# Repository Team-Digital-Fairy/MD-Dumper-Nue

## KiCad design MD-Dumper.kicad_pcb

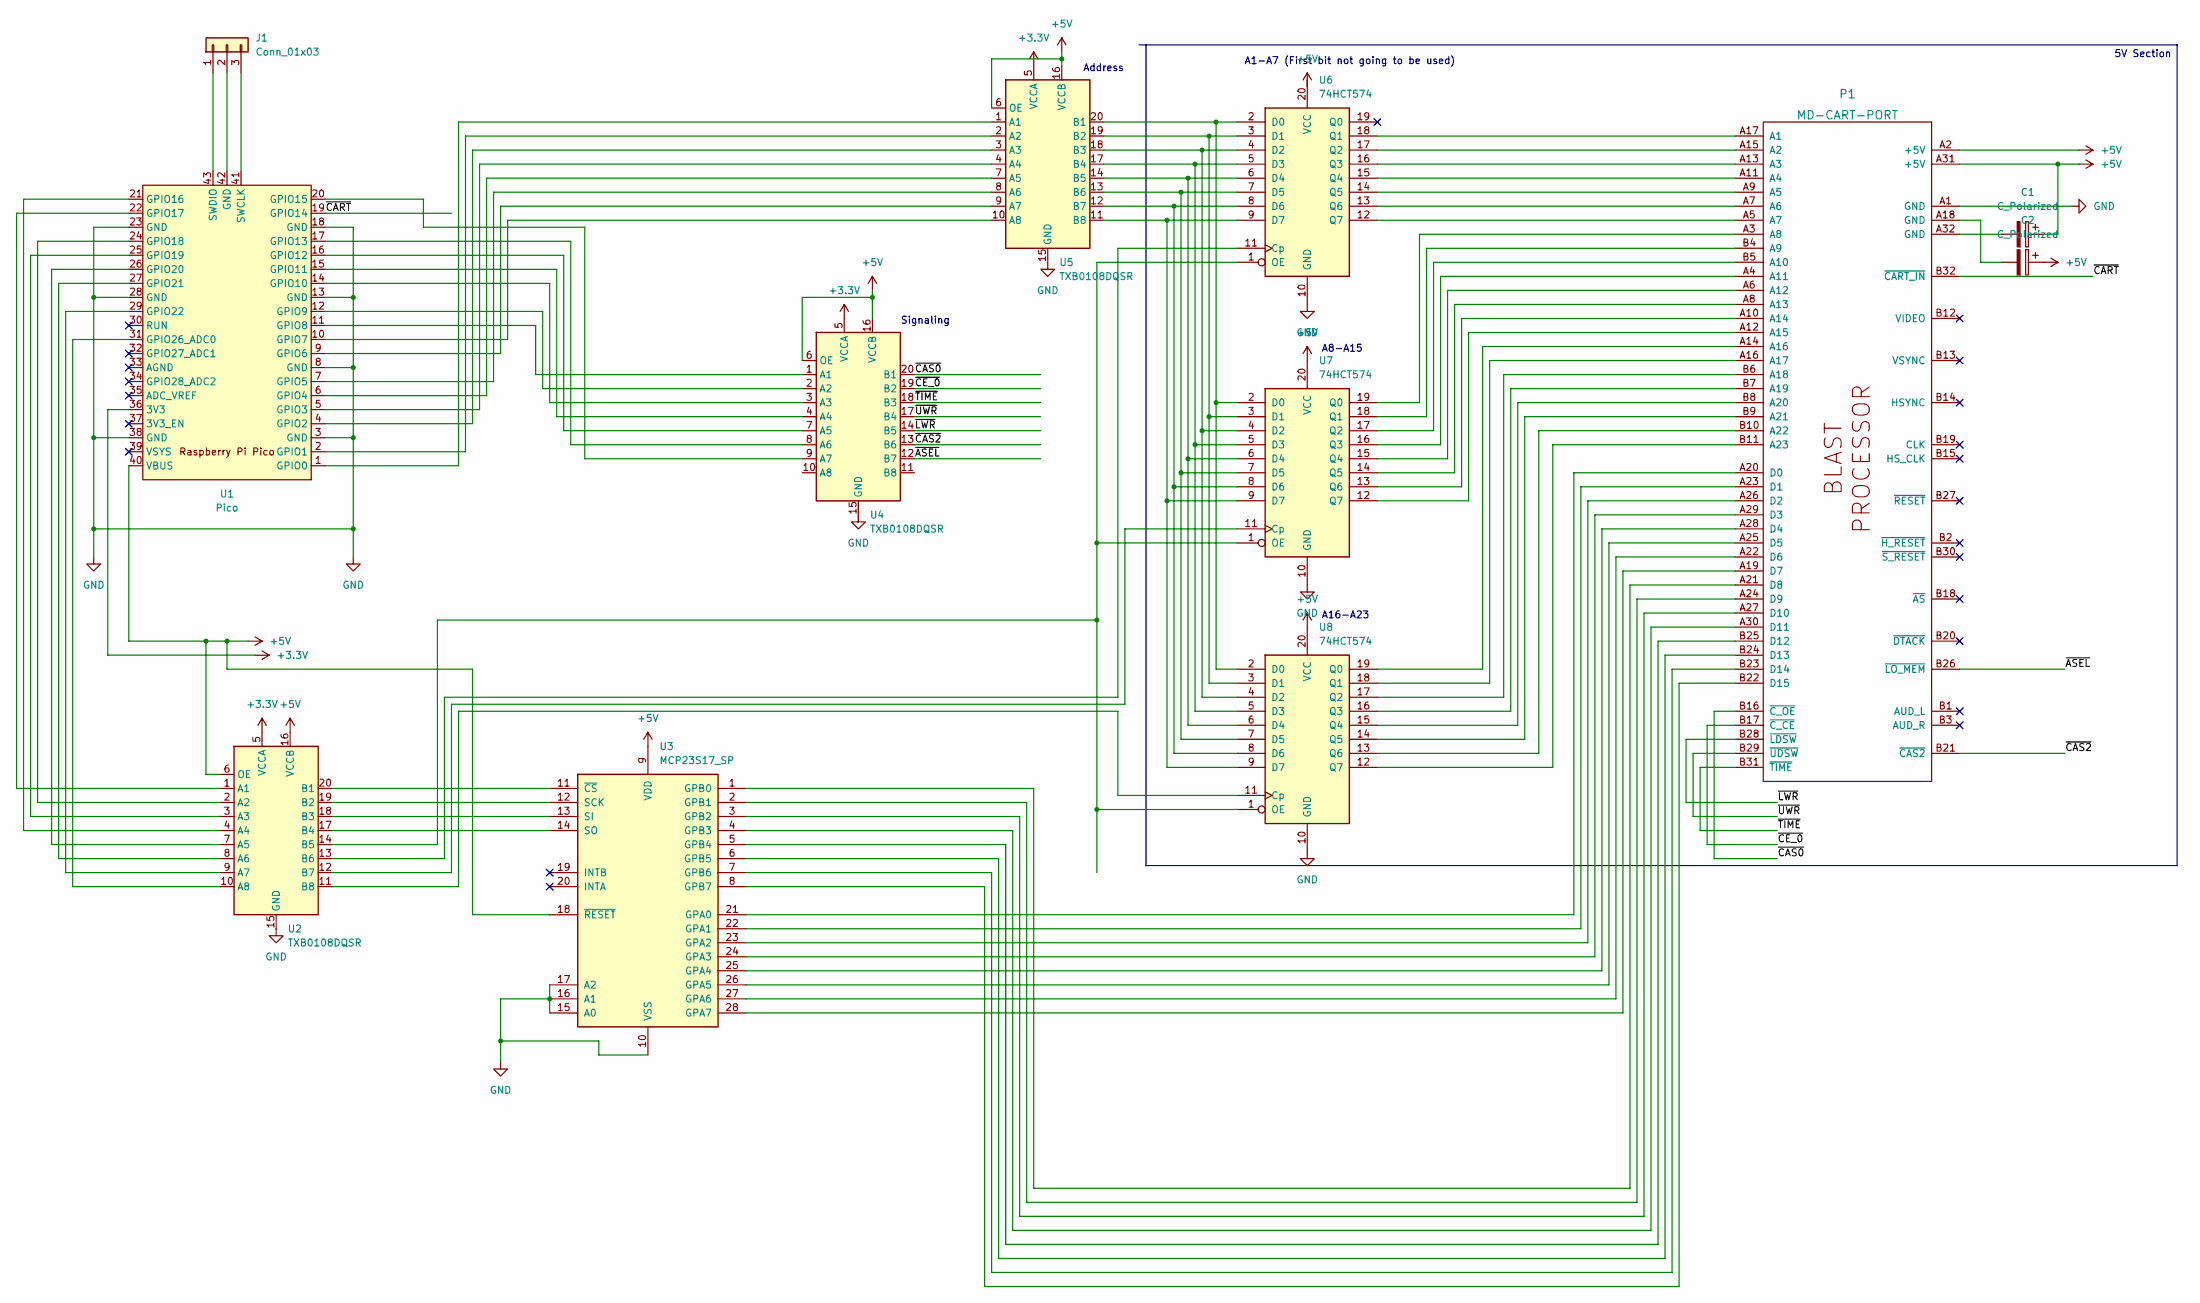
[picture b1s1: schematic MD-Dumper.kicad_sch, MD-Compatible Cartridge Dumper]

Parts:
C1, C2: C_Polarized; CP_Radial_D6.3mm_P2.50mm
J1: Conn_01x03; PinHeader_1x03_P2.54mm_Vertical
P1: MD-CART-PORT; GEN_CART_PORT
U1: Pico; RPi_Pico_SMD_TH
U2, U4, U5: TXB0108DQSR; txb0108e
U3: MCP23S17_SP; DIP-28_W7.62mm
U6, U7, U8: 74HCT574; DIP-20_W7.62mm_LongPads

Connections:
+3V3: U1.36 (3V3), U2.5 (VCCA), U4.5 (VCCA), U5.5 (VCCA)
+5V: C1.1, C2.1, P1.A2 (+5V), P1.A31 (+5V), U1.40 (VBUS), U2.6 (OE), U2.16 (VCCB), U3.9 (VDD), U3.18 (~RESET), U4.6 (OE), U4.16 (VCCB), U5.6 (OE), U5.16 (VCCB), U7.20 (VCC), U8.20 (VCC)
/~CAS0: P1.B16 (~C_OE), U4.20 (B1)
/~CAS2: P1.B21 (~CAS2), U4.13 (B6)
/~CE_0: P1.B17 (~C_CE), U4.19 (B2)
/~LWR: P1.B28 (~LDSW), U4.14 (B5)
/~TIME: P1.B31 (~TIME), U4.18 (B3)
/~UWR: P1.B29 (~UDSW), U4.17 (B4)
GND: P1.A1 (GND), U1.3 (GND), U1.8 (GND), U1.13 (GND), U1.18 (GND), U1.23 (GND), U1.28 (GND), U1.38 (GND), U2.15 (GND), U3.10 (VSS), U3.15 (A0), U3.16 (A1), U3.17 (A2), U4.15 (GND), U5.15 (GND), U6.10 (GND), U7.10 (GND), U8.10 (GND)
unnamed: P1.A3 (A8), U7.19 (Q0)
unnamed: P1.A4 (A11), U7.16 (Q3)
unnamed: P1.A5 (A7), U6.12 (Q7)
unnamed: P1.A6 (A12), U7.15 (Q4)
unnamed: P1.A7 (A6), U6.13 (Q6)
unnamed: P1.A8 (A13), U7.14 (Q5)
unnamed: P1.A9 (A5), U6.14 (Q5)
unnamed: P1.A10 (A14), U7.13 (Q6)
unnamed: P1.A11 (A4), U6.15 (Q4)
unnamed: P1.A12 (A15), U7.12 (Q7)
unnamed: P1.A13 (A3), U6.16 (Q3)
unnamed: P1.A14 (A16), U8.19 (Q0)
unnamed: P1.A15 (A2), U6.17 (Q2)
unnamed: P1.A16 (A17), U8.18 (Q1)
unnamed: P1.A17 (A1), U6.18 (Q1)
unnamed: C2.2, P1.A18 (GND)
unnamed: P1.A19 (D7), U3.28 (GPA7)
unnamed: P1.A20 (D0), U3.21 (GPA0)
unnamed: P1.A21 (D8), U3.1 (GPB0)
unnamed: P1.A22 (D6), U3.27 (GPA6)
unnamed: P1.A23 (D1), U3.22 (GPA1)
unnamed: P1.A24 (D9), U3.2 (GPB1)
unnamed: P1.A25 (D5), U3.26 (GPA5)
unnamed: P1.A26 (D2), U3.23 (GPA2)
unnamed: P1.A27 (D10), U3.3 (GPB2)
unnamed: P1.A28 (D4), U3.25 (GPA4)
unnamed: P1.A29 (D3), U3.24 (GPA3)
unnamed: P1.A30 (D11), U3.4 (GPB3)
unnamed: C1.2, P1.A32 (GND)
unnamed: P1.B4 (A9), U7.18 (Q1)
unnamed: P1.B5 (A10), U7.17 (Q2)
unnamed: P1.B6 (A18), U8.17 (Q2)
unnamed: P1.B7 (A19), U8.16 (Q3)
unnamed: P1.B8 (A20), U8.15 (Q4)
unnamed: P1.B9 (A21), U8.14 (Q5)
unnamed: P1.B10 (A22), U8.13 (Q6)
unnamed: P1.B11 (A23), U8.12 (Q7)
unnamed: P1.B22 (D15), U3.8 (GPB7)
unnamed: P1.B23 (D14), U3.7 (GPB6)
unnamed: P1.B24 (D13), U3.6 (GPB5)
unnamed: P1.B25 (D12), U3.5 (GPB4)
unnamed: U1.1 (GPIO0), U5.1 (A1)
unnamed: U1.2 (GPIO1), U5.2 (A2)
unnamed: U1.4 (GPIO2), U5.3 (A3)
unnamed: U1.5 (GPIO3), U5.4 (A4)
unnamed: U1.6 (GPIO4), U5.7 (A5)
unnamed: U1.7 (GPIO5), U5.8 (A6)
unnamed: U1.9 (GPIO6), U5.9 (A7)
unnamed: U1.10 (GPIO7), U5.10 (A8)
unnamed: U1.11 (GPIO8), U4.1 (A1)
unnamed: U1.12 (GPIO9), U4.2 (A2)
unnamed: U1.14 (GPIO10), U4.3 (A3)
unnamed: U1.15 (GPIO11), U4.4 (A4)
unnamed: U1.16 (GPIO12), U4.7 (A5)
unnamed: U1.17 (GPIO13), U4.8 (A6)
unnamed: U1.21 (GPIO16), U2.4 (A4)
unnamed: U1.22 (GPIO17), U2.1 (A1)
unnamed: U1.24 (GPIO18), U2.2 (A2)
unnamed: U1.25 (GPIO19), U2.3 (A3)
unnamed: J1.3, U1.41 (SWCLK)
unnamed: J1.2, U1.42 (GND)
unnamed: J1.1, U1.43 (SWDIO)
unnamed: U1.26 (GPIO20), U2.7 (A5)
unnamed: U1.27 (GPIO21), U2.8 (A6)
unnamed: U1.29 (GPIO22), U2.9 (A7)
unnamed: U1.31 (GPIO26_ADC0), U2.10 (A8)
unnamed: U2.11 (B8), U8.11 (Cp)
unnamed: U2.12 (B7), U7.11 (Cp)
unnamed: U2.17 (B4), U3.14 (SO)
unnamed: U2.18 (B3), U3.13 (SI)
unnamed: U2.19 (B2), U3.12 (SCK)
unnamed: U2.20 (B1), U3.11 (~CS)
unnamed: U5.11 (B8), U6.9 (D7), U7.9 (D7), U8.9 (D7)
unnamed: U5.12 (B7), U6.8 (D6), U7.8 (D6), U8.8 (D6)
unnamed: U5.13 (B6), U6.7 (D5), U7.7 (D5), U8.7 (D5)
unnamed: U5.14 (B5), U6.6 (D4), U7.6 (D4), U8.6 (D4)
unnamed: U5.17 (B4), U6.5 (D3), U7.5 (D3), U8.5 (D3)
unnamed: U5.18 (B3), U6.4 (D2), U7.4 (D2), U8.4 (D2)
unnamed: U5.19 (B2), U6.3 (D1), U7.3 (D1), U8.3 (D1)
unnamed: U5.20 (B1), U6.2 (D0), U7.2 (D0), U8.2 (D0)
unnamed: U2.14 (B5), U6.1 (OE), U7.1 (OE), U8.1 (OE)
unnamed: U2.13 (B6), U6.11 (Cp)

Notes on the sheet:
5V Section
A16-A23
Address
Signaling
A8-A15
A1-A7 (First bit not going to be used)

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
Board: 2 copper layers, 12 parts (0 on the bottom side), 95 nets, no tracks yet.
